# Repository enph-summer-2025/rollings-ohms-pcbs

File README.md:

# Rolling Ohms Robot

Designed by Joshua Himmens and Jack Polloway for the 2025 Engineering Physics Robot Summer competition.

## Brain Board
Main controller board handling all system logic and communication.

- **Project Directory**: [`brain/`](brain/)
- **Schematic**: [`renderings/Brain.pdf`](/renderings/Brain.pdf)

## H-Bridge Board
Dual H-Bride with electrical isolation and protection circuits.

- **Project Directory**: [`h-bridge/`](h-bridge/)
- **Schematic**: [`renderings/HBridge.pdf`](/renderings/HBridge.pdf)

## Power Distribution Board
Power distribution board to step a 16v LiPo to 5v and 9v and providing a soldering point for teh XT60 cable.

- **Project Directory**: [`power-distribution/`](power-distribution/)
- **Schematic**: [`renderings/Power_Board.pdf`](/renderings/Power_Board.pdf)

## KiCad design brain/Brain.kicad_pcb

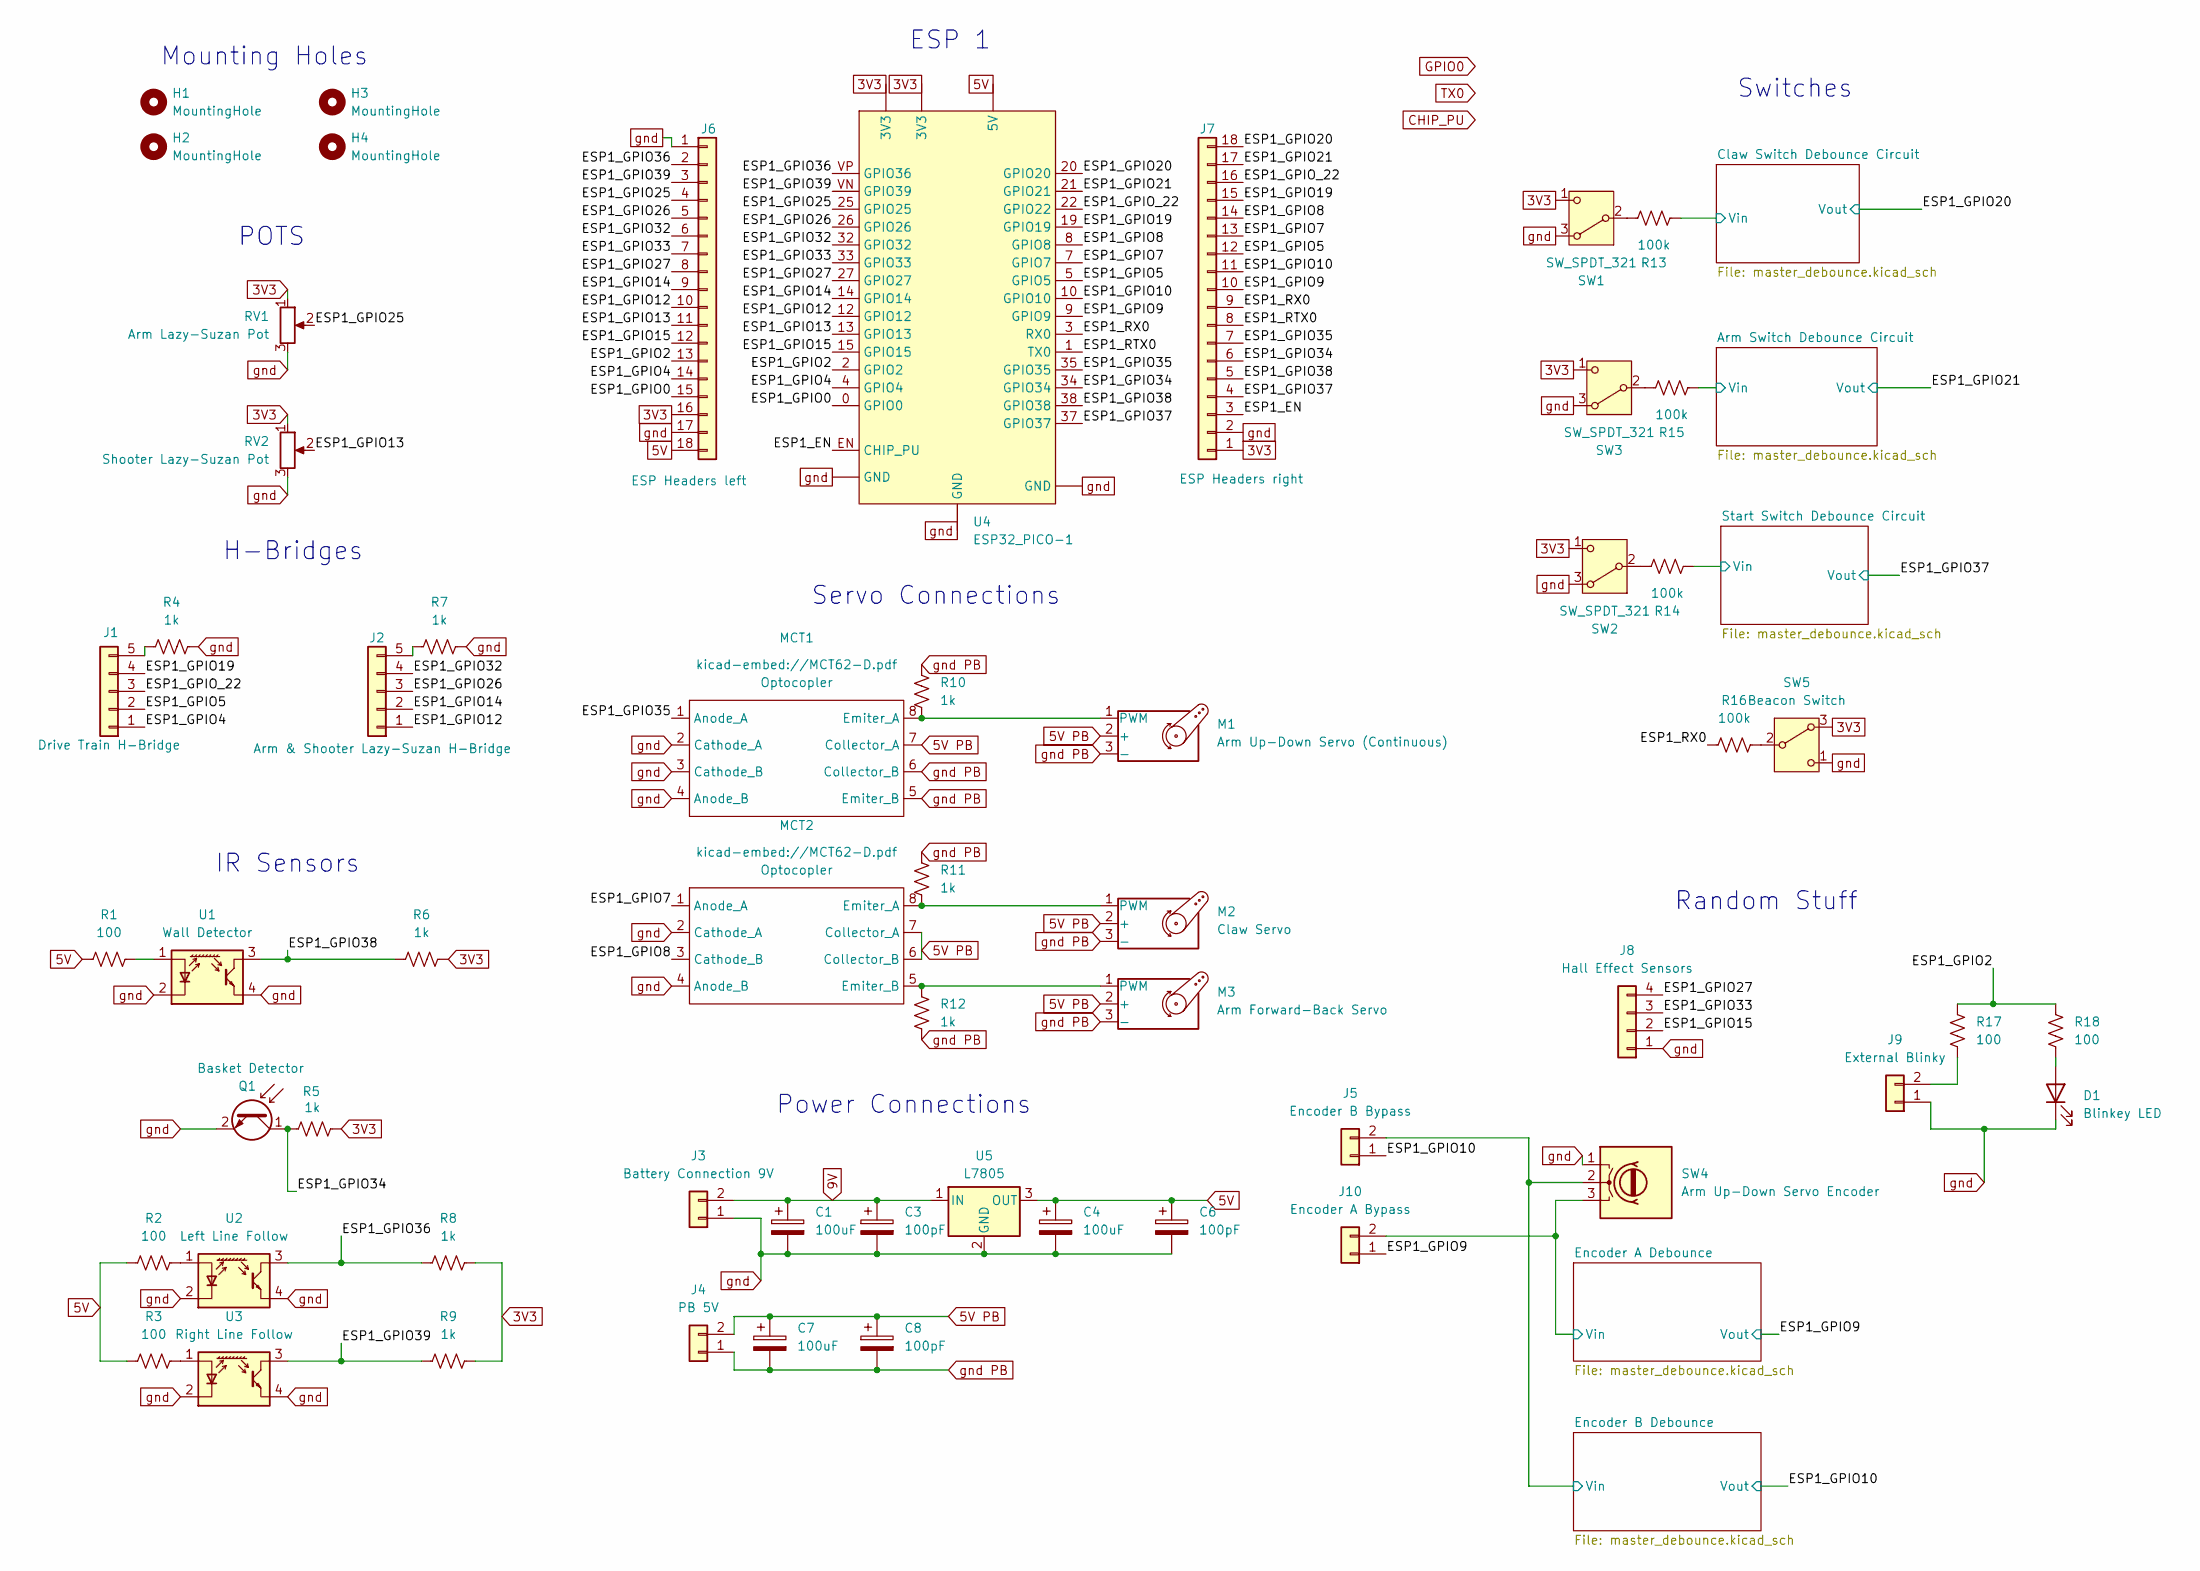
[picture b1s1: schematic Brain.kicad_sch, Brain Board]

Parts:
C1, C4, C7: 100uF; CP_Radial_D5.0mm_P2.50mm
C3, C6, C8: 100pF; CP_Radial_D5.0mm_P2.50mm
D1: Blinkey LED; LED_D5.0mm
H1, H2, H3, H4: MountingHole; MountingHole_3.2mm_M3
J1: Drive Train H-Bridge; PinHeader_1x05_P2.54mm_Vertical
J2: Arm & Shooter Lazy-Suzan H-Bridge; PinHeader_1x05_P2.54mm_Vertical
J3: Battery Connection 9V; PinHeader_1x02_P2.54mm_Vertical
J4: PB 5V; PinHeader_1x02_P2.54mm_Vertical
J5: Encoder B Bypass; PinHeader_1x02_P2.54mm_Vertical
J6: ESP Headers left; PinHeader_1x18_P2.54mm_Vertical
J7: ESP Headers right; PinHeader_1x18_P2.54mm_Vertical
J8: Hall Effect Sensors; PinHeader_1x04_P2.54mm_Vertical
J9: External Blinky; PinHeader_1x02_P2.54mm_Vertical
J10: Encoder A Bypass; PinHeader_1x02_P2.54mm_Vertical
M1: Arm Up-Down Servo (Continuous); PinHeader_1x03_P2.54mm_Vertical
M2: Claw Servo; PinHeader_1x03_P2.54mm_Vertical
M3: Arm Forward-Back Servo; PinHeader_1x03_P2.54mm_Vertical
MCT1, MCT2: DIP-8_W7.62mm
Q1: Basket Detector; PinHeader_1x02_P2.54mm_Vertical
R1, R2, R3, R17, R18: 100; R_Axial_DIN0411_L9.9mm_D3.6mm_P15.24mm_Horizontal
R4, R5, R6, R7, R8, R9, R10, R11, R12: 1k; R_Axial_DIN0411_L9.9mm_D3.6mm_P15.24mm_Horizontal
R13, R14, R15, R16: 100k; R_Axial_DIN0411_L9.9mm_D3.6mm_P15.24mm_Horizontal
RV1: Arm Lazy-Suzan Pot; PinHeader_1x03_P2.54mm_Vertical
RV2: Shooter Lazy-Suzan Pot; PinHeader_1x03_P2.54mm_Vertical
SW1, SW2, SW3: SW_SPDT_321; PinHeader_1x03_P2.54mm_Vertical
SW4: Arm Up-Down Servo Encoder; PinHeader_1x03_P2.54mm_Vertical
SW5: Beacon Switch; PinHeader_1x03_P2.54mm_Vertical
U1: Wall Detector; PinHeader_1x04_P2.54mm_Vertical
U2: Left Line Follow; PinHeader_1x04_P2.54mm_Vertical
U3: Right Line Follow; PinHeader_1x04_P2.54mm_Vertical
U4: ESP32_PICO-1; NEW_ESP32_PICO_1_DEV_KIT
U5: L7805; TO-220-3_Vertical

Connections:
3V3: J6.16, J7.1, R5.1, R6.2, R8.2, R9.1, RV1.1, RV2.1, SW1.1 (C), SW2.1 (C), SW3.1 (C), SW5.3 (A), U4.3V3; also elsewhere on the board
5V: C4.1, C6.1, J6.18, R1.1, R2.1, R3.1, U4.5V, U5.3 (OUT); also elsewhere on the board
5V PB: C7.1, C8.1, J4.2, M1.2 (+), M2.2 (+), M3.2 (+), MCT1.7 (Collector_A), MCT2.6 (Collector_B), MCT2.7 (Collector_A)
9V: C1.1, C3.1, J3.2, U5.1 (IN)
/Arm Switch Debounce Circuit/Vin: R15.1; also elsewhere on the board
/Claw Switch Debounce Circuit/Vin: R13.1; also elsewhere on the board
/ESP1_EN: J7.3, U4.EN (CHIP_PU)
/ESP1_GPIO0: J6.15, U4.0 (GPIO0)
/ESP1_GPIO2: J6.13, R17.1, R18.1, U4.2 (GPIO2)
/ESP1_GPIO4: J1.1, J6.14, U4.4 (GPIO4)
/ESP1_GPIO5: J1.2, J7.12, U4.5 (GPIO5)
/ESP1_GPIO7: J7.13, MCT2.1 (Anode_A), U4.7 (GPIO7)
/ESP1_GPIO8: J7.14, MCT2.3 (Cathode_B), U4.8 (GPIO8)
/ESP1_GPIO9: J7.10, J10.1, U4.9 (GPIO9); also elsewhere on the board
/ESP1_GPIO10: J5.1, J7.11, U4.10 (GPIO10); also elsewhere on the board
/ESP1_GPIO12: J2.1, J6.10, U4.12 (GPIO12)
/ESP1_GPIO13: J6.11, RV2.2, U4.13 (GPIO13)
/ESP1_GPIO14: J2.2, J6.9, U4.14 (GPIO14)
/ESP1_GPIO15: J6.12, J8.2, U4.15 (GPIO15)
/ESP1_GPIO19: J1.4, J7.15, U4.19 (GPIO19)
/ESP1_GPIO20: J7.18, U4.20 (GPIO20); also elsewhere on the board
/ESP1_GPIO21: J7.17, U4.21 (GPIO21); also elsewhere on the board
/ESP1_GPIO25: J6.4, RV1.2, U4.25 (GPIO25)
/ESP1_GPIO26: J2.3, J6.5, U4.26 (GPIO26)
/ESP1_GPIO27: J6.8, J8.4, U4.27 (GPIO27)
/ESP1_GPIO32: J2.4, J6.6, U4.32 (GPIO32)
/ESP1_GPIO33: J6.7, J8.3, U4.33 (GPIO33)
/ESP1_GPIO34: J7.6, Q1.1 (C), R5.2, U4.34 (GPIO34)
/ESP1_GPIO35: J7.7, MCT1.1 (Anode_A), U4.35 (GPIO35)
/ESP1_GPIO36: J6.2, R8.1, U2.3 (C), U4.VP (GPIO36)
/ESP1_GPIO37: J7.4, U4.37 (GPIO37); also elsewhere on the board
/ESP1_GPIO38: J7.5, R6.1, U1.3 (C), U4.38 (GPIO38)
/ESP1_GPIO39: J6.3, R9.2, U3.3 (C), U4.VN (GPIO39)
/ESP1_GPIO_22: J1.3, J7.16, U4.22 (GPIO22)
/ESP1_RTX0: J7.8, U4.1 (TX0)
/ESP1_RX0: J7.9, R16.1, U4.3 (RX0)
/Encoder A Debounce/Vin: J10.2, SW4.3; also elsewhere on the board
/Encoder B Debounce/Vin: J5.2, SW4.2; also elsewhere on the board
/Start Switch Debounce Circuit/Vin: R14.1; also elsewhere on the board
unnamed: D1.2 (A), R18.2
unnamed: J1.5, R4.2
unnamed: J2.5, R7.2
unnamed: J9.2, R17.2
unnamed: M1.1 (PWM), MCT1.8 (Emiter_A), R10.2
unnamed: M2.1 (PWM), MCT2.8 (Emiter_A), R11.2
unnamed: M3.1 (PWM), MCT2.5 (Emiter_B), R12.2
unnamed: R13.2, SW1.2 (B)
unnamed: R14.2, SW2.2 (B)
unnamed: R15.2, SW3.2 (B)
unnamed: R16.2, SW5.2 (B)
unnamed: R1.2, U1.1 (A)
unnamed: R2.2, U2.1 (A)
unnamed: R3.2, U3.1 (A)
gnd: C1.2, C3.2, C4.2, C6.2, D1.1 (K), J3.1, J6.1, J6.17, J7.2, J8.1, J9.1, MCT1.2 (Cathode_A), MCT1.3 (Cathode_B), MCT1.4 (Anode_B), MCT2.2 (Cathode_A), MCT2.4 (Anode_B), Q1.2 (E), R4.1, R7.1, RV1.3, RV2.3, SW1.3 (A), SW2.3 (A), SW3.3 (A), SW4.1, SW5.1 (C), U1.2 (K), U1.4 (E), U2.2 (K), U2.4 (E), U3.2 (K), U3.4 (E), U4.GND, U5.2 (GND); also elsewhere on the board
gnd PB: C7.2, C8.2, J4.1, M1.3 (-), M2.3 (-), M3.3 (-), MCT1.5 (Emiter_B), MCT1.6 (Collector_B), R10.1, R11.1, R12.1

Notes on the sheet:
POTS
IR Sensors
Servo Connections
H-Bridges
ESP 1
Mounting Holes
Switches
Random Stuff
Power Connections

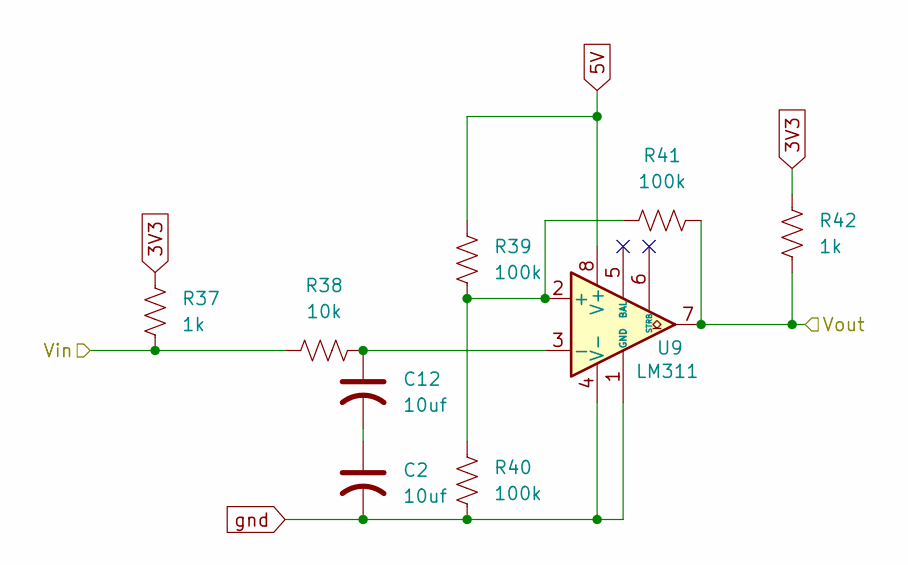
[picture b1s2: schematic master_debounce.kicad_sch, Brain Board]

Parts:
C2, C12: 10uf; CP_Radial_D5.0mm_P2.50mm
R37, R42: 1k; R_Axial_DIN0411_L9.9mm_D3.6mm_P15.24mm_Horizontal
R38: 10k; R_Axial_DIN0411_L9.9mm_D3.6mm_P15.24mm_Horizontal
R39, R40, R41: 100k; R_Axial_DIN0411_L9.9mm_D3.6mm_P15.24mm_Horizontal
U9: LM311; DIP-8_W7.62mm

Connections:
3V3: R37.1, R42.1; also elsewhere on the board
5V: R39.1, U9.8 (V+); also elsewhere on the board
/ESP1_GPIO9: R41.2, R42.2, U9.7; also elsewhere on the board
/Encoder A Debounce/Vin: R37.2, R38.1; also elsewhere on the board
unnamed: C2.1, C12.2
unnamed: R39.2, R40.2, R41.1, U9.2 (+)
unnamed: C12.1, R38.2, U9.3 (-)
gnd: C2.2, R40.1, U9.1 (GND), U9.4 (V-); also elsewhere on the board

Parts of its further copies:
C5, C9, C10, C11, C13, C14, C15, C16: 10uf; CP_Radial_D5.0mm_P2.50mm
R19, R24, R25, R30, R31, R36, R43, R48: 1k; R_Axial_DIN0411_L9.9mm_D3.6mm_P15.24mm_Horizontal
R20, R26, R32, R44: 10k; R_Axial_DIN0411_L9.9mm_D3.6mm_P15.24mm_Horizontal
R21, R22, R23, R27, R28, R29, R33, R34, R35, R45, R46, R47: 100k; R_Axial_DIN0411_L9.9mm_D3.6mm_P15.24mm_Horizontal
U6, U7, U8, U10: LM311; DIP-8_W7.62mm

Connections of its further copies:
3V3: R19.1, R24.1, R25.1, R30.1, R31.1, R36.1, R43.1, R48.1; also elsewhere on the board
5V: R21.1, R27.1, R33.1, R45.1, U6.8 (V+), U7.8 (V+), U8.8 (V+), U10.8 (V+); also elsewhere on the board
/Arm Switch Debounce Circuit/Vin: R25.2, R26.1; also elsewhere on the board
/Claw Switch Debounce Circuit/Vin: R19.2, R20.1; also elsewhere on the board
/ESP1_GPIO10: R47.2, R48.2, U10.7; also elsewhere on the board
/ESP1_GPIO20: R23.2, R24.2, U6.7; also elsewhere on the board
/ESP1_GPIO21: R29.2, R30.2, U7.7; also elsewhere on the board
/ESP1_GPIO37: R35.2, R36.2, U8.7; also elsewhere on the board
/Encoder B Debounce/Vin: R43.2, R44.1; also elsewhere on the board
/Start Switch Debounce Circuit/Vin: R31.2, R32.1; also elsewhere on the board
unnamed: C10.2, C15.1
unnamed: C11.2, C16.1
unnamed: C5.1, C13.2
unnamed: C9.2, C14.1
unnamed: R21.2, R22.2, R23.1, U6.2 (+)
unnamed: C9.1, R20.2, U6.3 (-)
unnamed: R27.2, R28.2, R29.1, U7.2 (+)
unnamed: C10.1, R26.2, U7.3 (-)
unnamed: R33.2, R34.2, R35.1, U8.2 (+)
unnamed: C11.1, R32.2, U8.3 (-)
unnamed: R45.2, R46.2, R47.1, U10.2 (+)
unnamed: C13.1, R44.2, U10.3 (-)
gnd: C5.2, C14.2, C15.2, C16.2, R22.1, R28.1, R34.1, R46.1, U6.1 (GND), U6.4 (V-), U7.1 (GND), U7.4 (V-), U8.1 (GND), U8.4 (V-), U10.1 (GND), U10.4 (V-); also elsewhere on the board

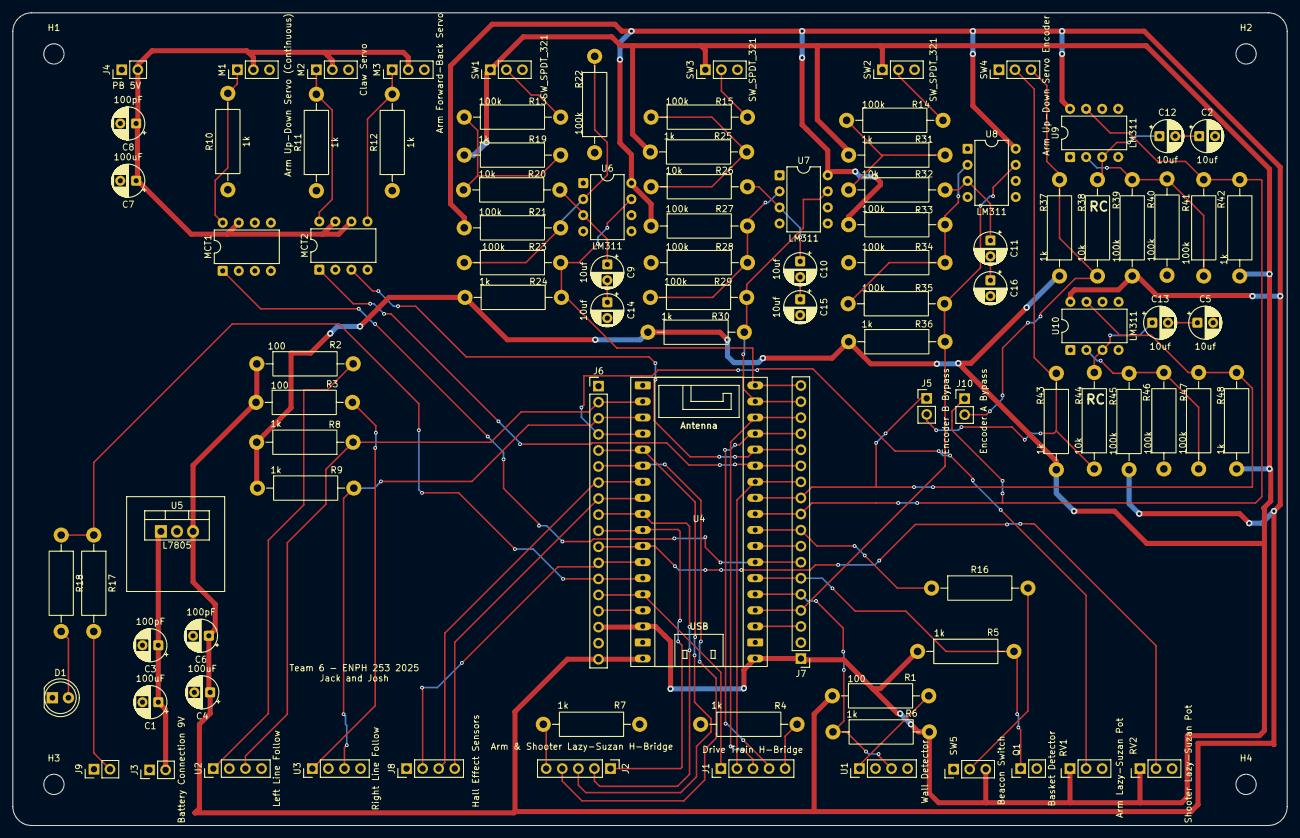
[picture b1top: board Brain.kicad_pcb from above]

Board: 2 copper layers, 201.5 x 128.5 mm, 102 parts (0 on the bottom side), 70 nets.

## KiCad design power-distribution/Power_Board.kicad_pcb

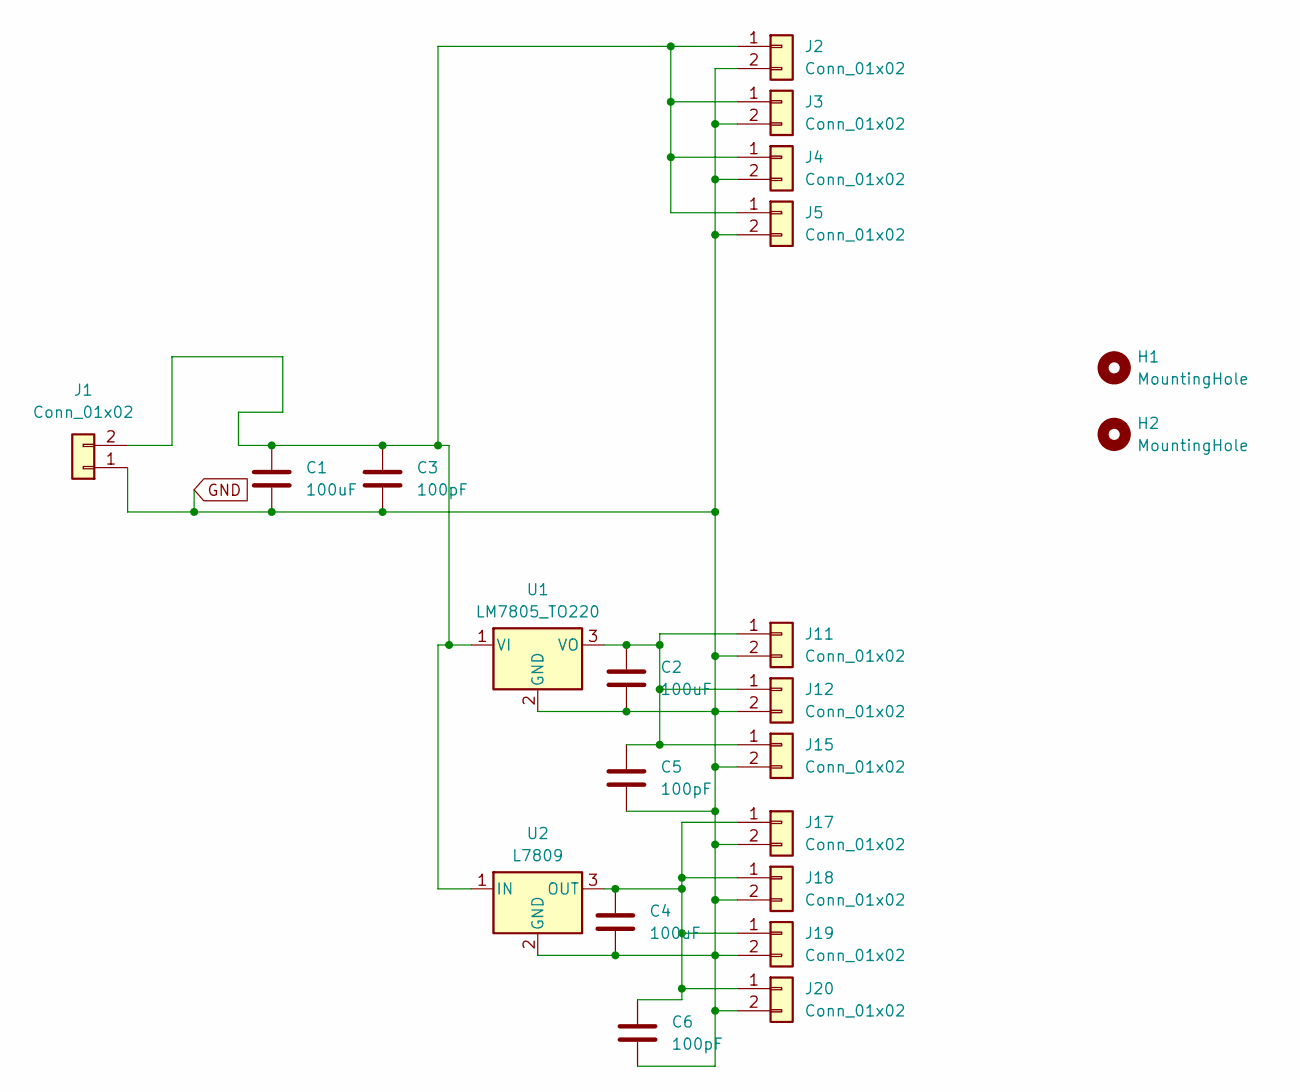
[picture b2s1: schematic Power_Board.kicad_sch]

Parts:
C1, C2, C4: 100uF
C3, C5, C6: 100pF
H1, H2: MountingHole; MountingHole_3.2mm_M3
J1: Conn_01x02; Untitled
J2, J3, J4, J5, J11, J12, J15, J17, J18, J19, J20: Conn_01x02; PinHeader_1x02_P2.54mm_Vertical
U1: LM7805_TO220; TO-220-3_Vertical
U2: L7809; TO-220-3_Vertical

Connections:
GND: C1.2, C2.2, C3.2, C4.2, C5.2, C6.2, J1.1, J2.2, J3.2, J4.2, J5.2, J11.2, J12.2, J15.2, J17.2, J18.2, J19.2, J20.2, U1.2 (GND), U2.2 (GND)
unnamed: C1.1, C3.1, J1.2, J2.1, J3.1, J4.1, J5.1, U1.1 (VI), U2.1 (IN)
unnamed: C2.1, C5.1, J11.1, J12.1, J15.1, U1.3 (VO)
unnamed: C4.1, C6.1, J17.1, J18.1, J19.1, J20.1, U2.3 (OUT)

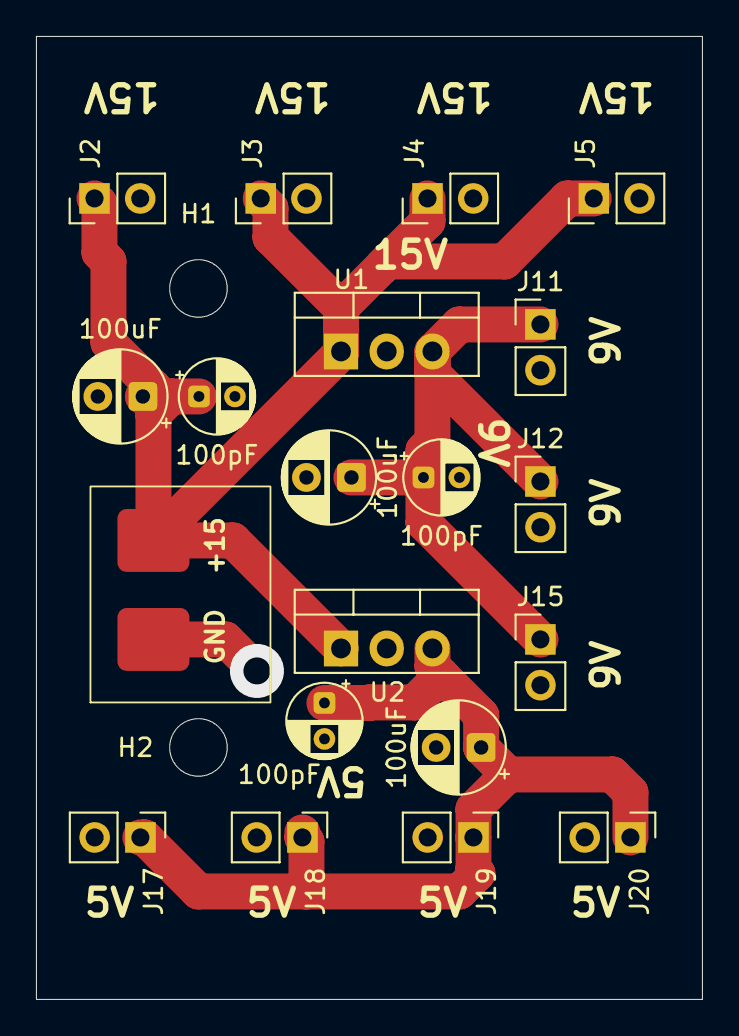
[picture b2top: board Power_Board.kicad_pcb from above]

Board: 2 copper layers, 37.0 x 53.5 mm, 22 parts (0 on the bottom side), 4 nets.

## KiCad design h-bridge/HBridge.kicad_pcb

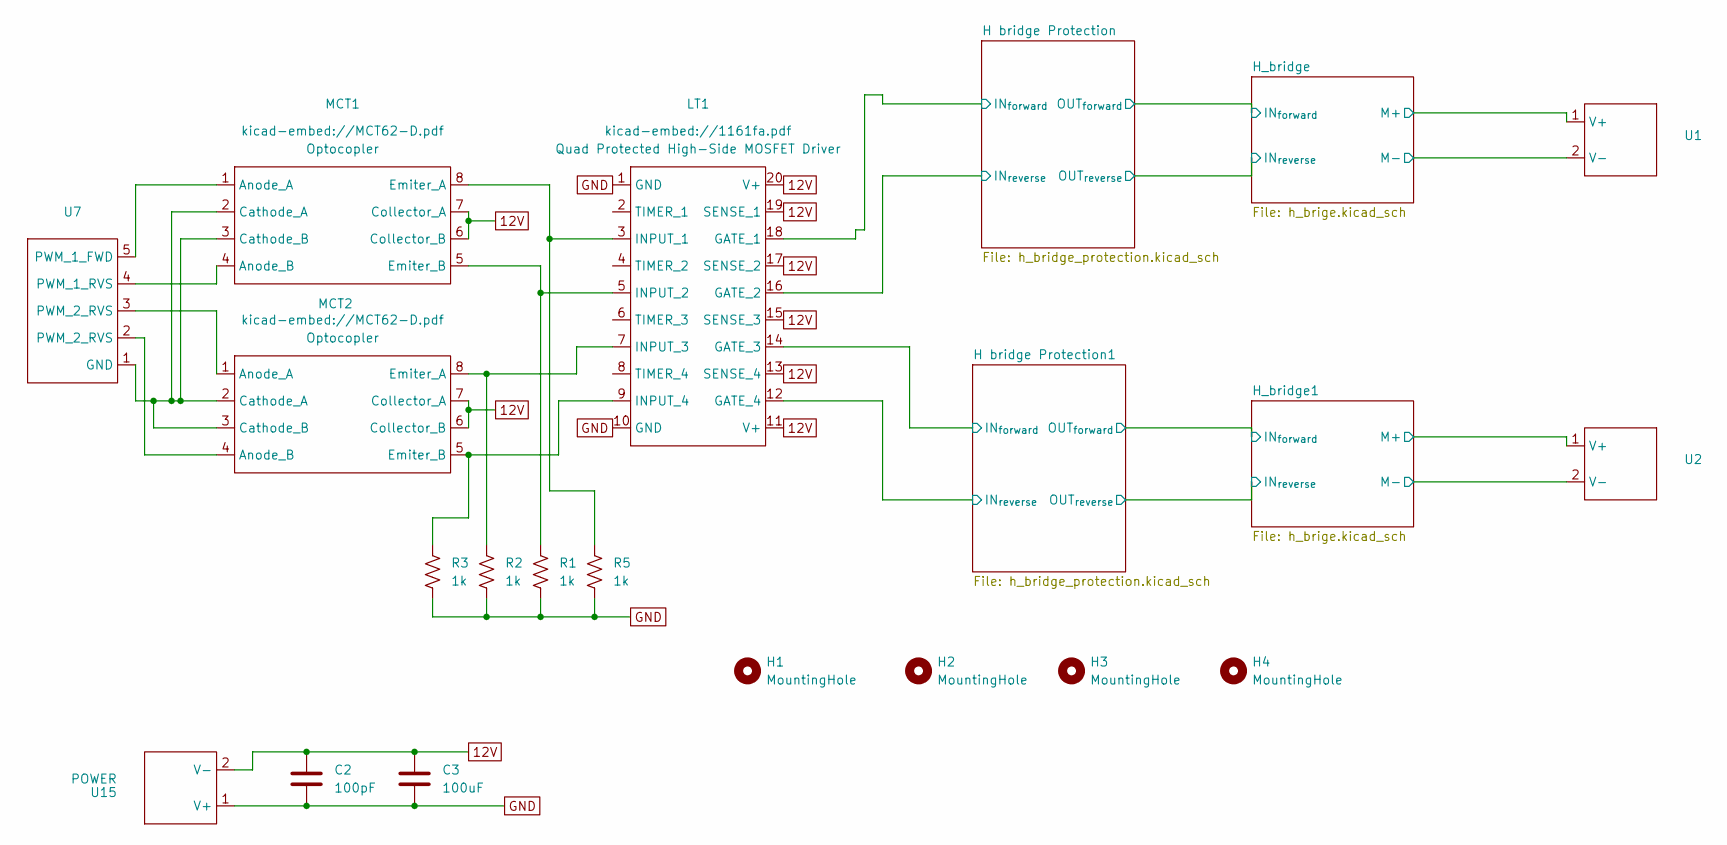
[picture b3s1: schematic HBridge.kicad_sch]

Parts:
C2: 100pF; CP_Radial_D4.0mm_P2.00mm
C3: 100uF; CP_Radial_D4.0mm_P2.00mm
H1, H2, H3, H4: MountingHole; MountingHole_3.2mm_M3
LT1: DIP-20_W7.62mm_Socket
MCT1, MCT2: DIP-8_W7.62mm_Socket
R1, R2, R3, R5: 1k; R_Axial_DIN0204_L3.6mm_D1.6mm_P5.08mm_Horizontal
U1, U2: PinHeader_1x02_P2.54mm_Vertical
U7: PinHeader_1x05_P2.54mm_Vertical
U15: POWER; PinHeader_1x02_P2.54mm_Vertical

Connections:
12V: C2.1, C3.1, LT1.11 (V+), LT1.13 (SENSE_4), LT1.15 (SENSE_3), LT1.17 (SENSE_2), LT1.19 (SENSE_1), LT1.20 (V+), MCT1.6 (Collector_B), MCT1.7 (Collector_A), MCT2.6 (Collector_B), MCT2.7 (Collector_A), U15.2 (V-); also elsewhere on the board
/H bridge Protection1/IN_{forward}: LT1.14 (GATE_3); also elsewhere on the board
/H bridge Protection1/IN_{reverse}: LT1.12 (GATE_4); also elsewhere on the board
/H bridge Protection/IN_{forward}: LT1.18 (GATE_1); also elsewhere on the board
/H bridge Protection/IN_{reverse}: LT1.16 (GATE_2); also elsewhere on the board
/H_bridge1/M+: U2.1 (V+); also elsewhere on the board
/H_bridge1/M-: U2.2 (V-); also elsewhere on the board
/H_bridge/M+: U1.1 (V+); also elsewhere on the board
/H_bridge/M-: U1.2 (V-); also elsewhere on the board
GND: C2.2, C3.2, LT1.1 (GND), LT1.10 (GND), R1.2, R2.2, R3.2, R5.2, U15.1 (V+); also elsewhere on the board
unnamed: LT1.3 (INPUT_1), MCT1.8 (Emiter_A), R5.1
unnamed: LT1.5 (INPUT_2), MCT1.5 (Emiter_B), R1.1
unnamed: LT1.7 (INPUT_3), MCT2.8 (Emiter_A), R2.1
unnamed: LT1.9 (INPUT_4), MCT2.5 (Emiter_B), R3.1
unnamed: MCT1.1 (Anode_A), U7.5 (PWM_1_FWD)
unnamed: MCT1.4 (Anode_B), U7.4 (PWM_1_RVS)
unnamed: MCT1.2 (Cathode_A), MCT1.3 (Cathode_B), MCT2.2 (Cathode_A), MCT2.3 (Cathode_B), U7.1 (GND)
unnamed: MCT2.1 (Anode_A), U7.3 (PWM_2_RVS)
unnamed: MCT2.4 (Anode_B), U7.2 (PWM_2_RVS)

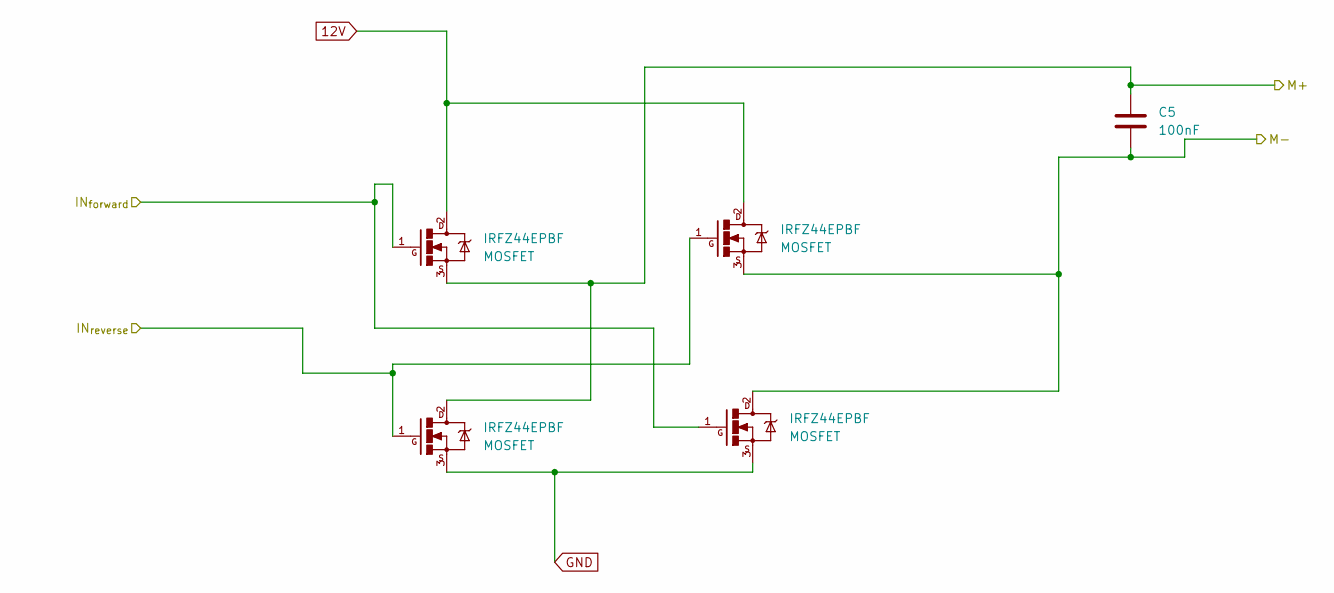
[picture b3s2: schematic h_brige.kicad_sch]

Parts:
C5: 100nF; CP_Radial_D4.0mm_P2.00mm
U16, U17, U18, U19: IRFZ44EPBF; TO-220-3_Vertical

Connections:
12V: U16.2, U18.2; also elsewhere on the board
/H bridge Protection/IN_{forward}: U17.1, U18.1; also elsewhere on the board
/H bridge Protection/IN_{reverse}: U16.1, U19.1; also elsewhere on the board
/H_bridge/M+: C5.1, U16.3, U17.2; also elsewhere on the board
/H_bridge/M-: C5.2, U18.3, U19.2; also elsewhere on the board
GND: U17.3, U19.3; also elsewhere on the board

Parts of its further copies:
C1: 100nF; CP_Radial_D4.0mm_P2.00mm
U3, U4, U5, U6: IRFZ44EPBF; TO-220-3_Vertical

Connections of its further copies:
12V: U3.2, U5.2; also elsewhere on the board
/H bridge Protection1/IN_{forward}: U4.1, U5.1; also elsewhere on the board
/H bridge Protection1/IN_{reverse}: U3.1, U6.1; also elsewhere on the board
/H_bridge1/M+: C1.1, U3.3, U4.2; also elsewhere on the board
/H_bridge1/M-: C1.2, U5.3, U6.2; also elsewhere on the board
GND: U4.3, U6.3; also elsewhere on the board

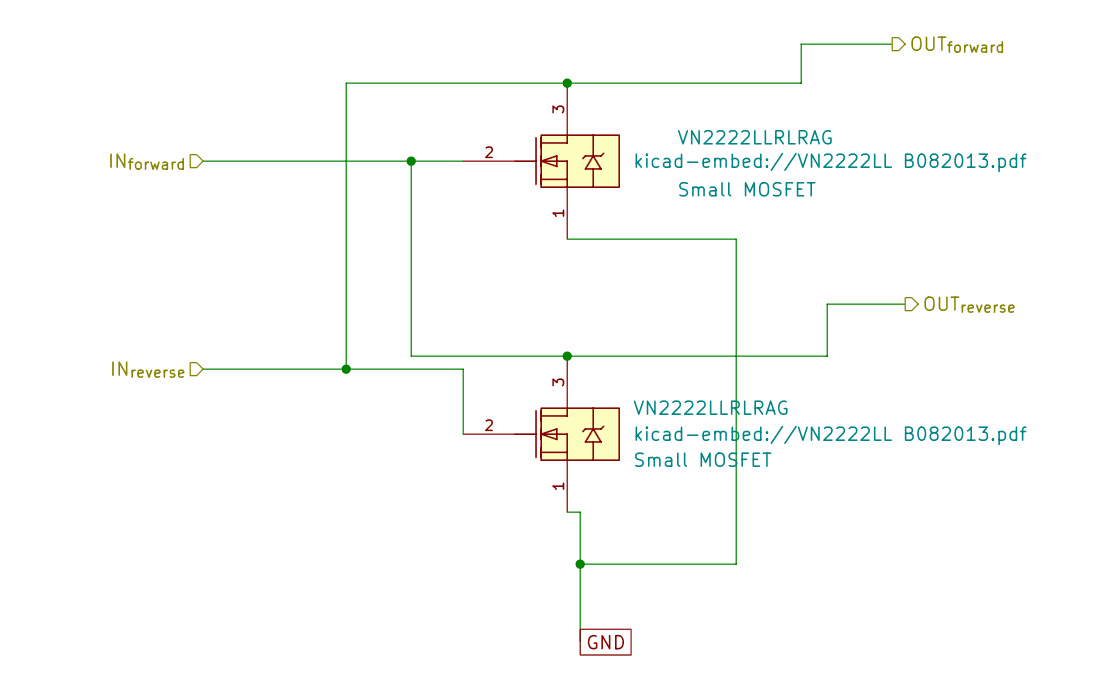
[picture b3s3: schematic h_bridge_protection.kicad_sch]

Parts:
Q5, Q6: VN2222LLRLRAG; TO-92_HandSolder

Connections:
/H bridge Protection/IN_{forward}: Q5.2, Q6.3; also elsewhere on the board
/H bridge Protection/IN_{reverse}: Q5.3, Q6.2; also elsewhere on the board
GND: Q5.1, Q6.1; also elsewhere on the board

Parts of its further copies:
Q1, Q2: VN2222LLRLRAG; TO-92_HandSolder

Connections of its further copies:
/H bridge Protection1/IN_{forward}: Q1.2, Q2.3; also elsewhere on the board
/H bridge Protection1/IN_{reverse}: Q1.3, Q2.2; also elsewhere on the board
GND: Q1.1, Q2.1; also elsewhere on the board

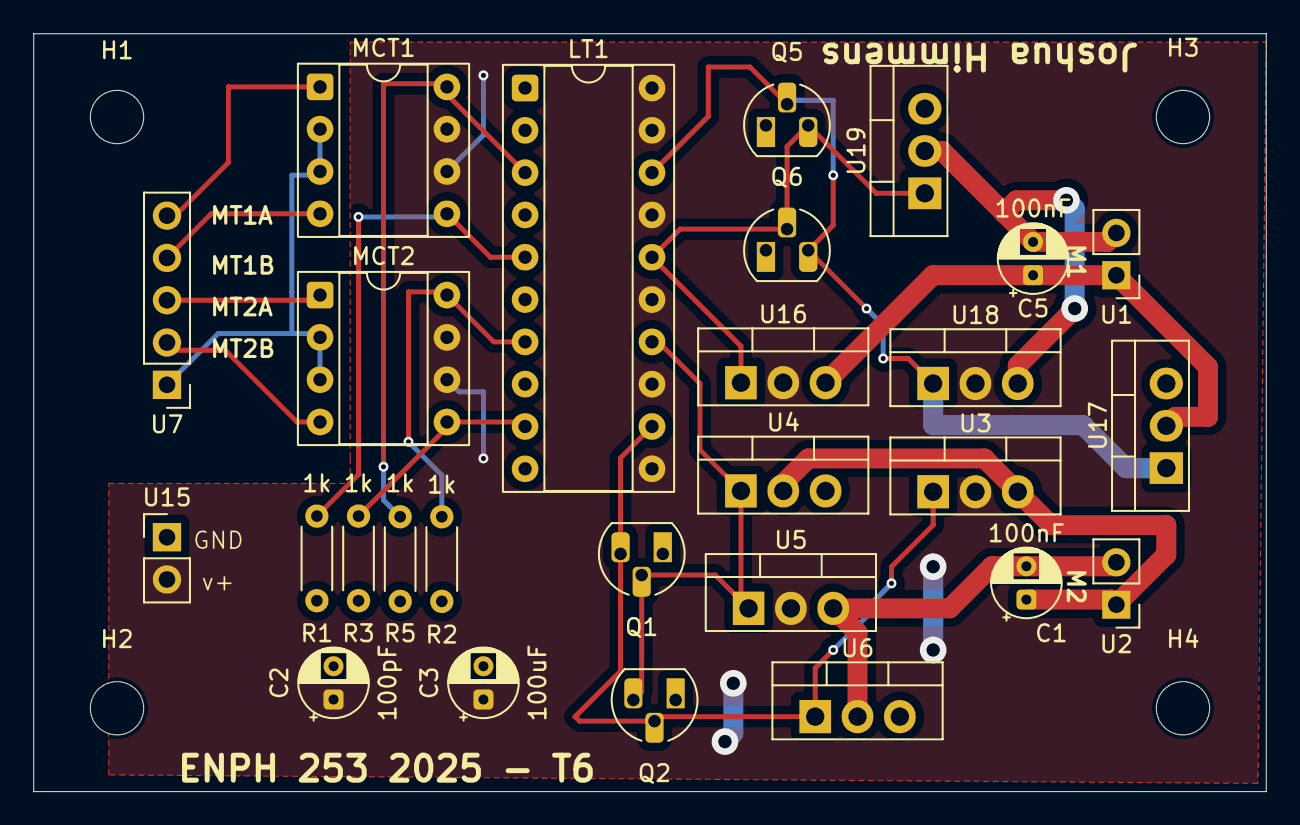
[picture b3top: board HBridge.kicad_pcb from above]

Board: 2 copper layers, 74.0 x 45.5 mm, 31 parts (0 on the bottom side), 19 nets.

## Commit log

2025-07-15 move over designs
2025-07-15 add pipeline
2025-07-15 fix pipeline
2025-07-15 fix pipeline... again
2025-07-15 fix pipeline... again and again
2025-07-15 fix pipeline... why even have a pipeline at this point
2025-07-15 only error on errors
2025-07-15 releases need to work
2025-07-16 ready for publication, remove CI
2025-07-16 update pd board schematic
